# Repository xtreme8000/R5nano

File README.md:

# R5 nano

Single board computer with future Linux support, mostly intended for use as a lightweight server.

Planned SoC implementation using LiteX featuring a RISC-V CPU and 64MiB RAM.

## Gateware

TODO

## Software

Work in progress.

Firmware supports bitstream upload over USB to the FPGA at the moment.

## Hardware

* iCE40UP5k FPGA, 5280 LUTs
* 64MiB SD-RAM
* microSD card for storage
* USB port for connectivity like ethernet
* USB-C port for power, bitstream upload
* STM32F103 for initial bitstream load from either USB-C or microSD
* Debug header with FPGA+STM32 GPIO, SWD for STM32
* 52x52mm (~2x2in) board

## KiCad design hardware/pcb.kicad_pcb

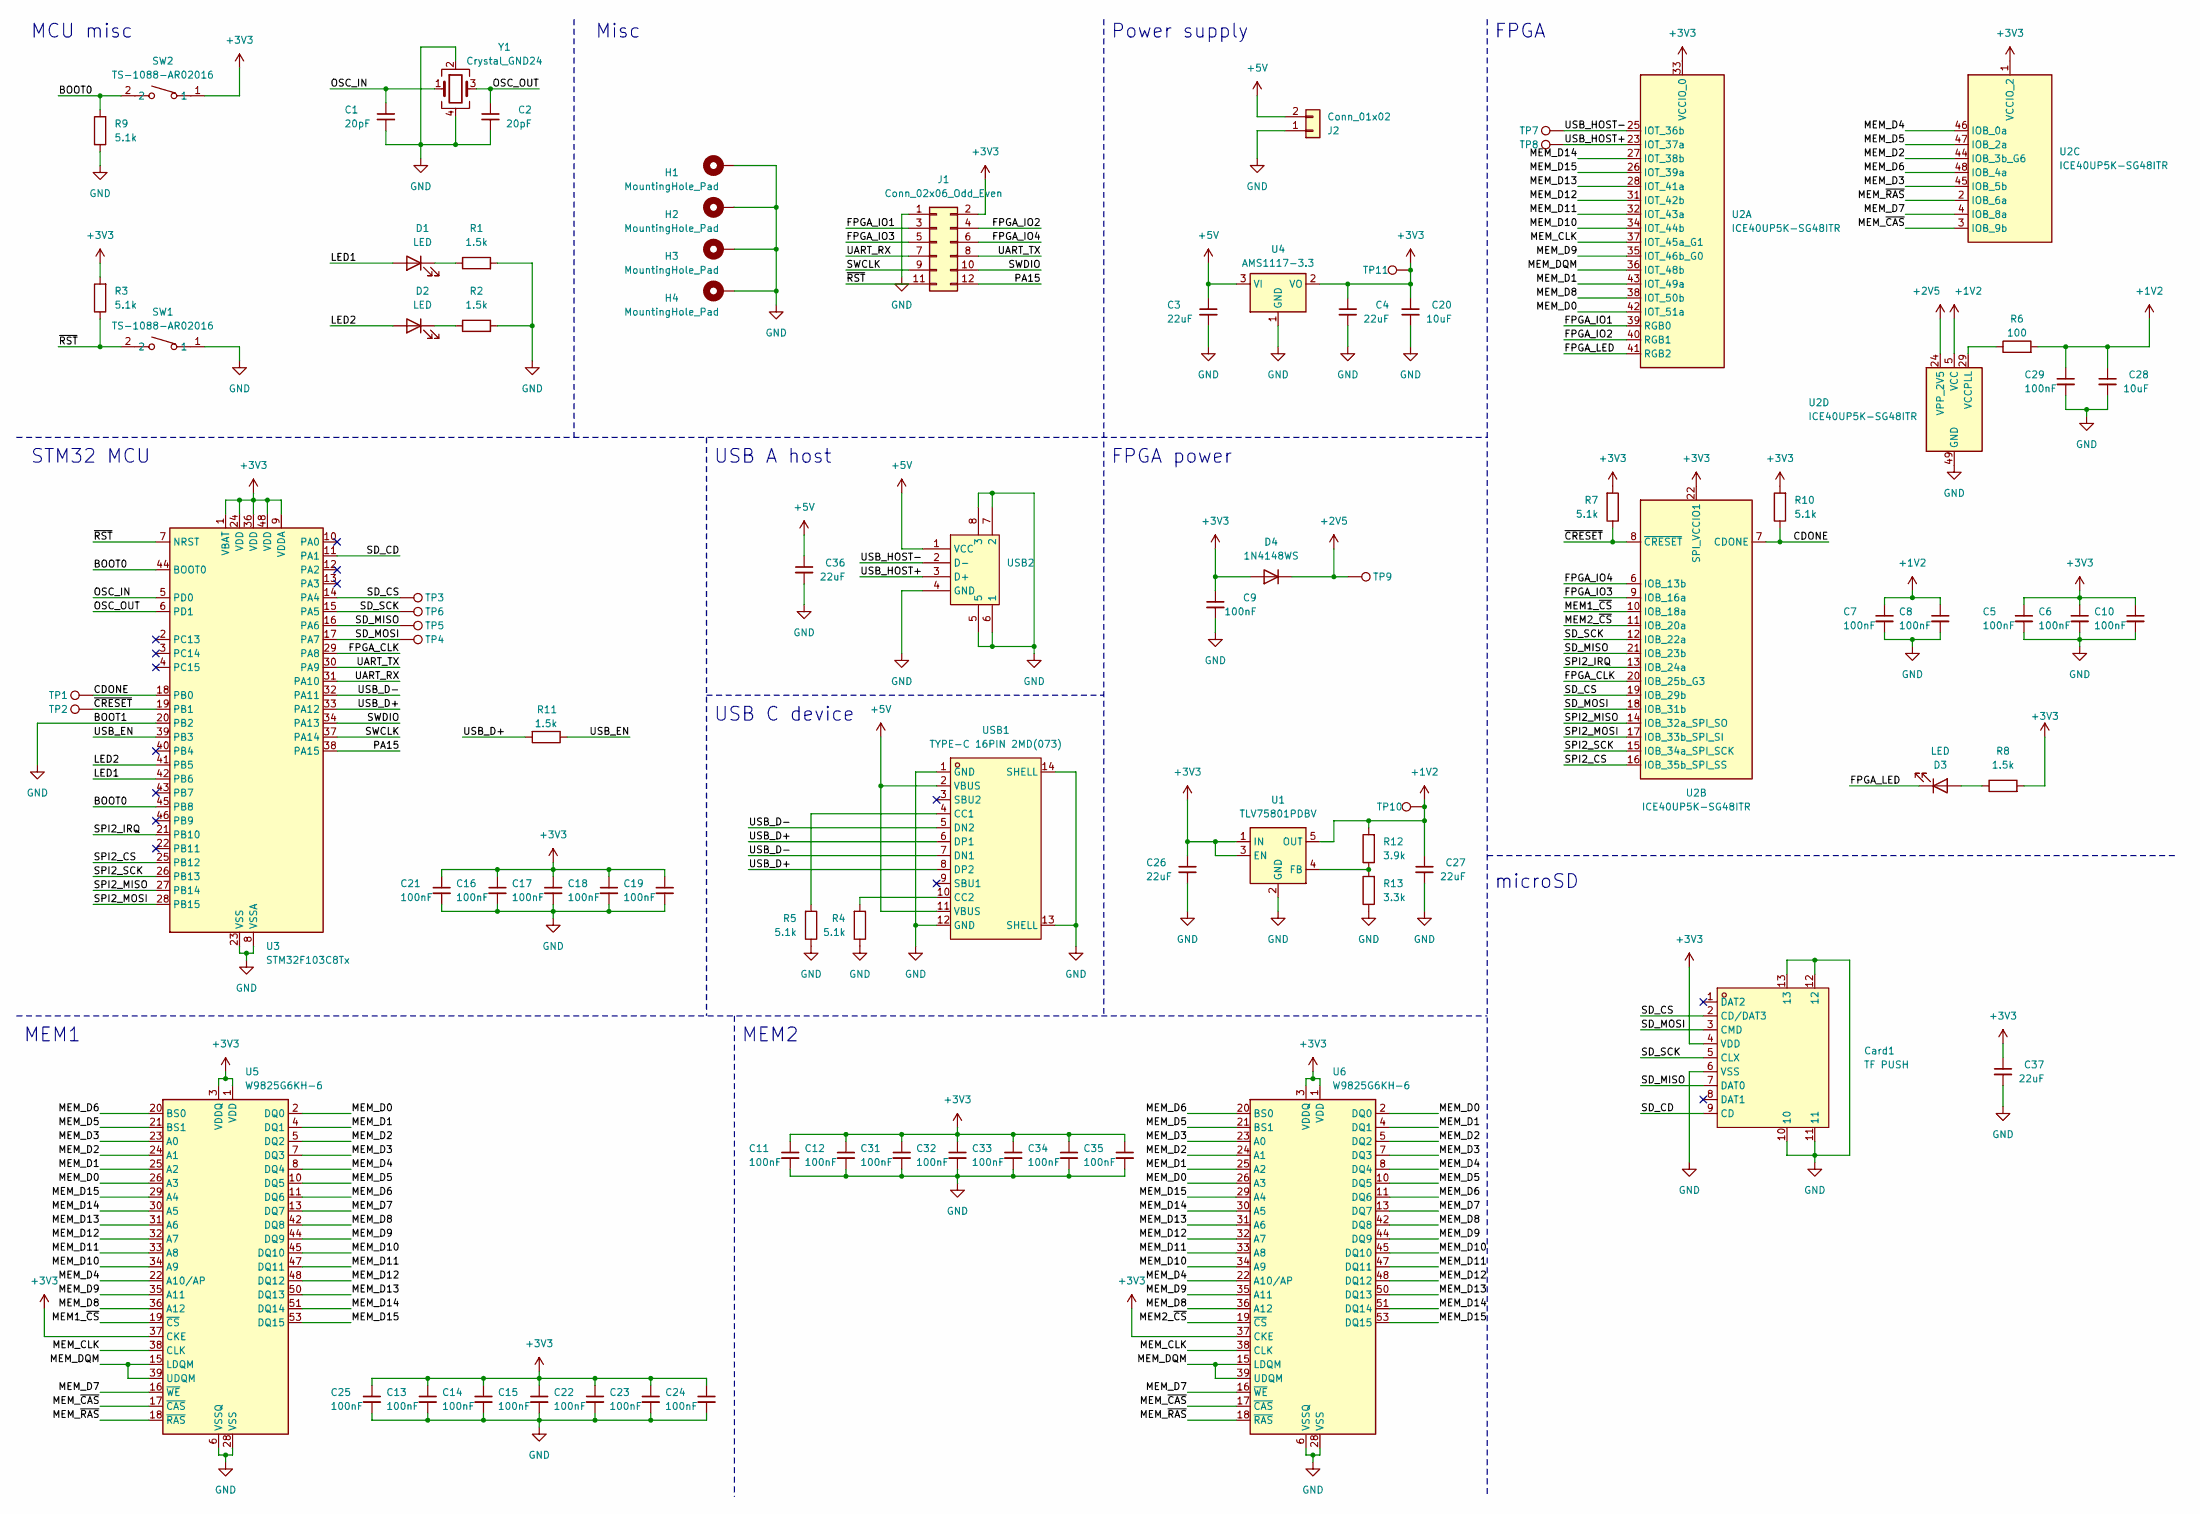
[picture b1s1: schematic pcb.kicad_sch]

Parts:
C1, C2: 20pF; C_0603_1608Metric; LCSC Part C1648
C3, C4, C26, C27, C36, C37: 22uF; C_0603_1608Metric; LCSC Part C59461
C5, C6, C7, C8, C9, C10, C11, C12, C13, C14, C15, C16, C17, C18, C19, C21, C22, C23, C24, C25, C29, C31, C32, C33, C34, C35: 100nF; C_0402_1005Metric; LCSC Part C1525
C20, C28: 10uF; C_0402_1005Metric; LCSC Part C15525
Card1: TF PUSH; TF-SMD_TF-PUSH; LCSC Part C393941
D1, D2, D3: LED; LED_0603_1608Metric; LCSC Part C2286
D4: 1N4148WS; D_SOD-323; LCSC Part C2128
H1, H2, H3, H4: MountingHole_Pad; MountingHole_2.2mm_M2_DIN965_Pad
J1: Conn_02x06_Odd_Even; PinHeader_2x06_P2.54mm_Vertical
J2: Conn_01x02; PinHeader_1x02_P2.54mm_Vertical
R1, R2, R8, R11: 1.5k; R_0603_1608Metric; LCSC Part C22843
R3, R4, R5, R7, R9, R10: 5.1k; R_0603_1608Metric; LCSC Part C23186
R6: 100; R_0402_1005Metric; LCSC Part C25076
R12: 3.9k; R_0603_1608Metric; LCSC Part C23018
R13: 3.3k; R_0603_1608Metric; LCSC Part C22978
SW1, SW2: TS-1088-AR02016; SW-SMD_L3.9-W3.0-P4.45; LCSC Part C720477
TP1, TP2, TP3, TP4, TP5, TP6, TP7, TP8, TP9, TP10, TP11: TestPoint; TestPoint_Pad_D2.0mm
U1: TLV75801PDBV; SOT-23-5; LCSC Part C2877852
U2: ICE40UP5K-SG48ITR; QFN-48-1EP_7x7mm_P0.5mm_EP5.6x5.6mm; LCSC Part C2678152
U3: STM32F103C8Tx; LQFP-48_7x7mm_P0.5mm; LCSC Part C8734
U4: AMS1117-3.3; SOT-223-3_TabPin2; LCSC Part C6186
U5, U6: W9825G6KH-6; TSOP-II-54_22.2x10.16mm_P0.8mm; LCSC Part C62246
USB1: TYPE-C 16PIN 2MD(073); USB-C-SMD_TYPE-C-6PIN-2MD-073; LCSC Part C2765186
USB2: USB-A-SMD_USB-M-21; LCSC Part C42474
Y1: Crystal_GND24; Crystal_SMD_3225-4Pin_3.2x2.5mm; LCSC Part C9002

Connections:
+1V2: C7.1, C8.1, C27.1, C28.1, C29.1, R6.2, R12.2, TP10.1, U1.5 (OUT), U2.5 (VCC), U2.30 (VCC)
+2V5: D4.1 (K), TP9.1, U2.24 (VPP_2V5)
+3V3: C4.1, C5.1, C6.1, C9.1, C10.1, C11.1, C12.1, C13.1, C14.1, C15.1, C16.1, C17.1, C18.1, C19.1, C20.1, C21.1, C22.1, C23.1, C24.1, C25.1, C26.1, C31.1, C32.1, C33.1, C34.1, C35.1, C37.1, Card1.4 (VDD), D4.2 (A), J1.2, R3.2, R7.2, R8.2, R10.2, SW2.1, TP11.1, U1.1 (IN), U1.3 (EN), U2.1 (VCCIO_2), U2.22 (SPI_VCCIO1), U2.33 (VCCIO_0), U3.1 (VBAT), U3.9 (VDDA), U3.24 (VDD), U3.36 (VDD), U3.48 (VDD), U4.2 (VO), U5.1 (VDD), U5.3 (VDDQ), U5.9 (VDDQ), U5.14 (VDD), U5.27 (VDD), U5.37 (CKE), U5.43 (VDDQ), U5.49 (VDDQ), U6.1 (VDD), U6.3 (VDDQ), U6.9 (VDDQ), U6.14 (VDD), U6.27 (VDD), U6.37 (CKE), U6.43 (VDDQ), U6.49 (VDDQ)
+5V: C3.1, C36.1, J2.2, U4.3 (VI), USB1.2 (VBUS), USB1.11 (VBUS), USB2.1 (VCC)
/BOOT0: R9.2, SW2.2, U3.44 (BOOT0), U3.45 (PB8)
/CDONE: R10.1, TP1.1, U2.7 (CDONE), U3.18 (PB0)
/FPGA_CLK: U2.20 (IOB_25b_G3), U3.29 (PA8)
/FPGA_IO1: J1.3, U2.39 (RGB0)
/FPGA_IO2: J1.4, U2.40 (RGB1)
/FPGA_IO3: J1.5, U2.9 (IOB_16a)
/FPGA_IO4: J1.6, U2.6 (IOB_13b)
/FPGA_LED: D3.1 (K), U2.41 (RGB2)
/LED1: D1.2 (A), U3.42 (PB6)
/LED2: D2.2 (A), U3.41 (PB5)
/MEM1_~CS: U2.10 (IOB_18a), U5.19 (~CS)
/MEM2_~CS: U2.11 (IOB_20a), U6.19 (~CS)
/MEM_CLK: U2.37 (IOT_45a_G1), U5.38 (CLK), U6.38 (CLK)
/MEM_D0: U2.42 (IOT_51a), U5.2 (DQ0), U5.26 (A3), U6.2 (DQ0), U6.26 (A3)
/MEM_D1: U2.43 (IOT_49a), U5.4 (DQ1), U5.25 (A2), U6.4 (DQ1), U6.25 (A2)
/MEM_D2: U2.44 (IOB_3b_G6), U5.5 (DQ2), U5.24 (A1), U6.5 (DQ2), U6.24 (A1)
/MEM_D3: U2.45 (IOB_5b), U5.7 (DQ3), U5.23 (A0), U6.7 (DQ3), U6.23 (A0)
/MEM_D4: U2.46 (IOB_0a), U5.8 (DQ4), U5.22 (A10/AP), U6.8 (DQ4), U6.22 (A10/AP)
/MEM_D5: U2.47 (IOB_2a), U5.10 (DQ5), U5.21 (BS1), U6.10 (DQ5), U6.21 (BS1)
/MEM_D6: U2.48 (IOB_4a), U5.11 (DQ6), U5.20 (BS0), U6.11 (DQ6), U6.20 (BS0)
/MEM_D7: U2.4 (IOB_8a), U5.13 (DQ7), U5.16 (~WE), U6.13 (DQ7), U6.16 (~WE)
/MEM_D8: U2.38 (IOT_50b), U5.36 (A12), U5.42 (DQ8), U6.36 (A12), U6.42 (DQ8)
/MEM_D9: U2.35 (IOT_46b_G0), U5.35 (A11), U5.44 (DQ9), U6.35 (A11), U6.44 (DQ9)
/MEM_D10: U2.34 (IOT_44b), U5.34 (A9), U5.45 (DQ10), U6.34 (A9), U6.45 (DQ10)
/MEM_D11: U2.32 (IOT_43a), U5.33 (A8), U5.47 (DQ11), U6.33 (A8), U6.47 (DQ11)
/MEM_D12: U2.31 (IOT_42b), U5.32 (A7), U5.48 (DQ12), U6.32 (A7), U6.48 (DQ12)
/MEM_D13: U2.28 (IOT_41a), U5.31 (A6), U5.50 (DQ13), U6.31 (A6), U6.50 (DQ13)
/MEM_D14: U2.27 (IOT_38b), U5.30 (A5), U5.51 (DQ14), U6.30 (A5), U6.51 (DQ14)
/MEM_D15: U2.26 (IOT_39a), U5.29 (A4), U5.53 (DQ15), U6.29 (A4), U6.53 (DQ15)
/MEM_DQM: U2.36 (IOT_48b), U5.15 (LDQM), U5.39 (UDQM), U6.15 (LDQM), U6.39 (UDQM)
/MEM_~CAS: U2.3 (IOB_9b), U5.17 (~CAS), U6.17 (~CAS)
/MEM_~RAS: U2.2 (IOB_6a), U5.18 (~RAS), U6.18 (~RAS)
/OSC_IN: C1.1, U3.5 (PD0), Y1.1
/OSC_OUT: C2.1, U3.6 (PD1), Y1.3
/PA15: J1.12, U3.38 (PA15)
/SD_CD: Card1.9 (CD), U3.11 (PA1)
/SD_CS: Card1.2 (CD/DAT3), TP3.1, U2.19 (IOB_29b), U3.14 (PA4)
/SD_MISO: Card1.7 (DAT0), TP5.1, U2.21 (IOB_23b), U3.16 (PA6)
/SD_MOSI: Card1.3 (CMD), TP4.1, U2.18 (IOB_31b), U3.17 (PA7)
/SD_SCK: Card1.5 (CLX), TP6.1, U2.12 (IOB_22a), U3.15 (PA5)
/SPI2_CS: U2.16 (IOB_35b_SPI_SS), U3.25 (PB12)
/SPI2_IRQ: U2.13 (IOB_24a), U3.21 (PB10)
/SPI2_MISO: U2.14 (IOB_32a_SPI_SO), U3.27 (PB14)
/SPI2_MOSI: U2.17 (IOB_33b_SPI_SI), U3.28 (PB15)
/SPI2_SCK: U2.15 (IOB_34a_SPI_SCK), U3.26 (PB13)
/SWCLK: J1.9, U3.37 (PA14)
/SWDIO: J1.10, U3.34 (PA13)
/UART_RX: J1.7, U3.31 (PA10)
/UART_TX: J1.8, U3.30 (PA9)
/USB_D+: R11.2, U3.33 (PA12), USB1.6 (DP1), USB1.8 (DP2)
/USB_D-: U3.32 (PA11), USB1.5 (DN2), USB1.7 (DN1)
/USB_EN: R11.1, U3.39 (PB3)
/USB_HOST+: TP8.1, U2.23 (IOT_37a), USB2.3 (D+)
/USB_HOST-: TP7.1, U2.25 (IOT_36b), USB2.2 (D-)
/~CRESET: R7.1, TP2.1, U2.8 (~CRESET), U3.19 (PB1)
/~RST: J1.11, R3.1, SW1.2, U3.7 (NRST)
GND: C1.2, C2.2, C3.2, C4.2, C5.2, C6.2, C7.2, C8.2, C9.2, C10.2, C11.2, C12.2, C13.2, C14.2, C15.2, C16.2, C17.2, C18.2, C19.2, C20.2, C21.2, C22.2, C23.2, C24.2, C25.2, C26.2, C27.2, C28.2, C29.2, C31.2, C32.2, C33.2, C34.2, C35.2, C36.2, C37.2, Card1.6 (VSS), Card1.10, Card1.11, Card1.12, Card1.13, H1.1, H2.1, H3.1, H4.1, J1.1, J2.1, R1.2, R2.2, R4.1, R5.1, R9.1, R13.1, SW1.1, U1.2 (GND), U2.49 (GND), U3.8 (VSSA), U3.20 (PB2), U3.23 (VSS), U3.35 (VSS), U3.47 (VSS), U4.1 (GND), U5.6 (VSSQ), U5.12 (VSSQ), U5.28 (VSS), U5.41 (VSS), U5.46 (VSSQ), U5.52 (VSSQ), U5.54 (VSS), U6.6 (VSSQ), U6.12 (VSSQ), U6.28 (VSS), U6.41 (VSS), U6.46 (VSSQ), U6.52 (VSSQ), U6.54 (VSS), USB1.1 (GND), USB1.12 (GND), USB1.13 (SHELL), USB1.14 (SHELL), USB2.4 (GND), USB2.5, USB2.6 (1), USB2.7 (2), USB2.8 (3), Y1.2, Y1.4
unnamed: D1.1 (K), R1.1
unnamed: D2.1 (K), R2.1
unnamed: D3.2 (A), R8.1
unnamed: R12.1, R13.2, U1.4 (FB)
unnamed: R6.1, U2.29 (VCCPLL)
unnamed: R5.2, USB1.4 (CC1)
unnamed: R4.2, USB1.10 (CC2)

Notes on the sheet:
microSD
MEM1
Misc
STM32 MCU
USB A host
MCU misc
MEM2
USB C device
Power supply
FPGA power
FPGA

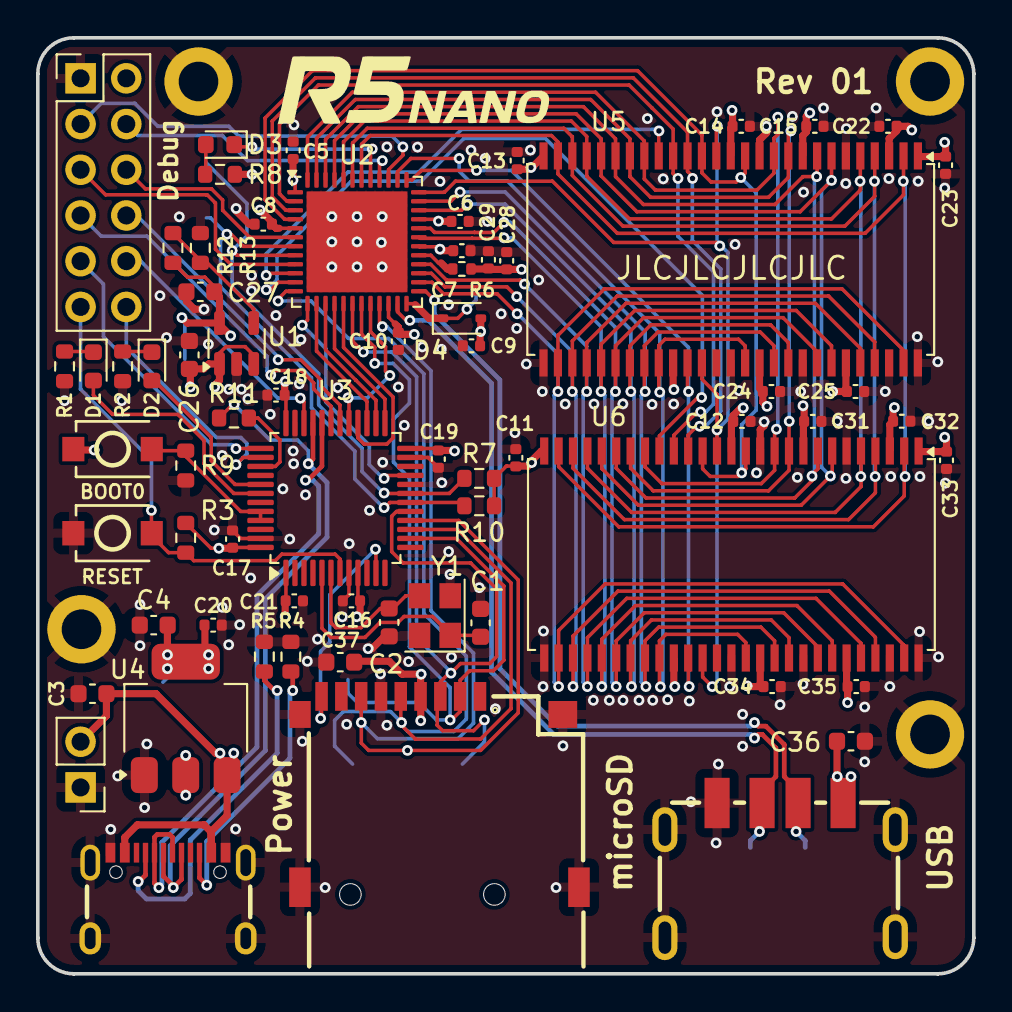
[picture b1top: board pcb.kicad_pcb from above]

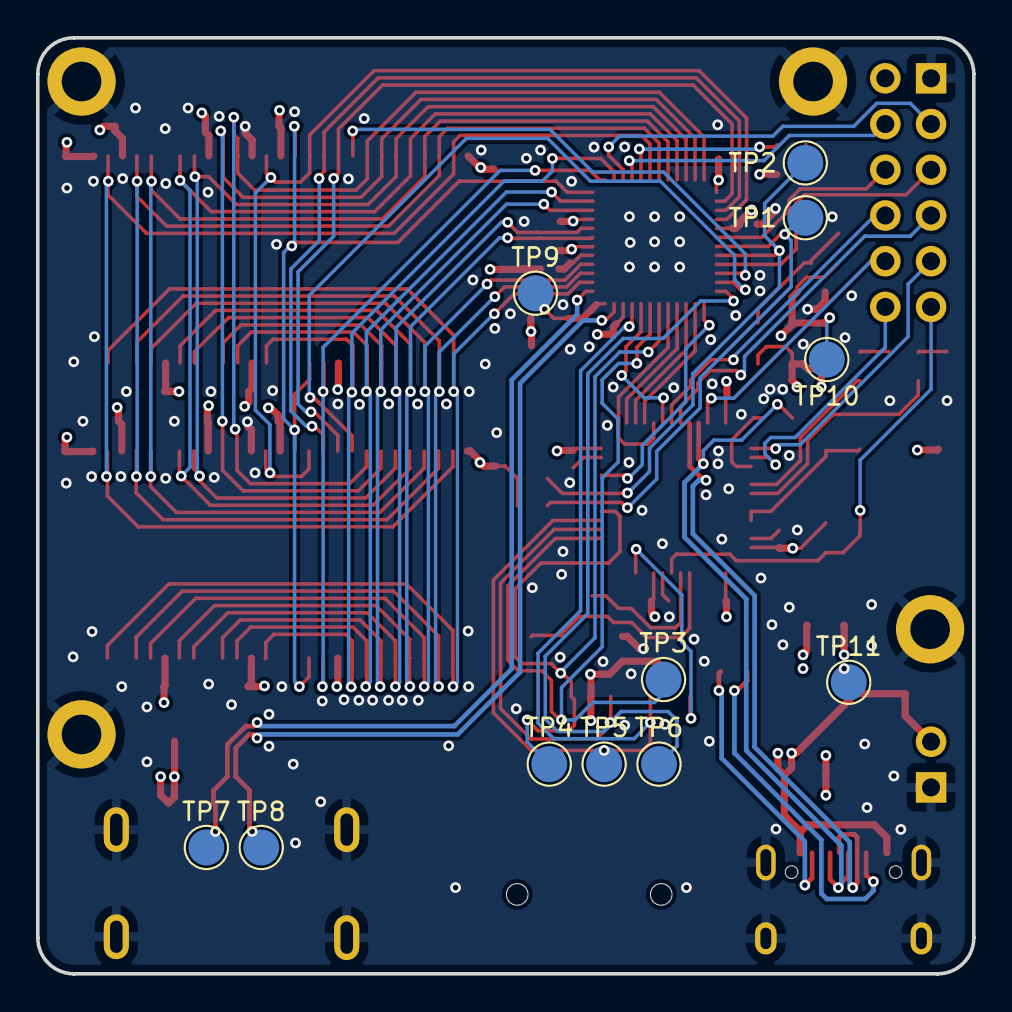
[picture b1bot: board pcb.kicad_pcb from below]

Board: 4 copper layers, 52.0 x 52.0 mm, 82 parts (11 on the bottom side), 68 nets.

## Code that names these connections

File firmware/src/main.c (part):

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#define PIN_SPI_SS GPIO12

#define PORT_CDONE GPIOB
#define PIN_CDONE GPIO0

#define PORT_USB_EN GPIOB
#define PIN_USB_EN GPIO3

#define PORT_LED1 GPIOB
#define PIN_LED1 GPIO6

#define PORT_LED2 GPIOB
#define PIN_LED2 GPIO5

uint8_t usbd_control_buffer[64]; // buffer for control requests

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}

void task_usb(void* args) {
	gpio_clear(PORT_USB_EN, PIN_USB_EN);
	vTaskDelay(pdMS_TO_TICKS(100));
	gpio_set(PORT_USB_EN, PIN_USB_EN);

	usbd_device* usbd_dev = usbd_init(
		&st_usbfs_v1_usb_driver, &dev_descr, &usb_config, usb_strings, 2,
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
void task_blink(void* args) {
	while(1) {
		gpio_toggle(PORT_LED1, PIN_LED1);
		vTaskDelay(pdMS_TO_TICKS(500));
	}
}
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		payload_transmitted = 0;
		xQueueSend(available_buffers, &e, portMAX_DELAY);

		gpio_set(PORT_LED2, PIN_LED2);

		gpio_clear(PORT_CRESET_B, PIN_CRESET_B);
		gpio_clear(PORT_SPI_SS, PIN_SPI_SS);
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
		spi_wait_idle(SPI2);

		uint8_t success = gpio_get(PORT_CDONE, PIN_CDONE) ? 1 : 0;
		xQueueSend(usb_host_interrupt, &success, portMAX_DELAY);

		gpio_clear(PORT_LED2, PIN_LED2);
	}
}

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
	// usb setup
	gpio_set_mode(PORT_USB_EN, GPIO_MODE_OUTPUT_2_MHZ, GPIO_CNF_OUTPUT_PUSHPULL,
				  PIN_USB_EN);
	gpio_clear(PORT_USB_EN, PIN_USB_EN);

	// blink setup
	gpio_set_mode(PORT_LED1, GPIO_MODE_OUTPUT_2_MHZ, GPIO_CNF_OUTPUT_PUSHPULL,
				  PIN_LED1);
	gpio_clear(PORT_LED1, PIN_LED1);
	gpio_set_mode(PORT_LED2, GPIO_MODE_OUTPUT_2_MHZ, GPIO_CNF_OUTPUT_PUSHPULL,
				  PIN_LED2);
	gpio_clear(PORT_LED2, PIN_LED2);

	// upload setup
	rcc_periph_clock_enable(RCC_SPI2);
	rcc_periph_clock_enable(RCC_DMA1);

	gpio_set_mode(GPIO_BANK_SPI2_SCK, GPIO_MODE_OUTPUT_50_MHZ,
				  GPIO_CNF_OUTPUT_ALTFN_PUSHPULL, GPIO_SPI2_SCK);
	gpio_set_mode(GPIO_BANK_SPI2_MOSI, GPIO_MODE_OUTPUT_50_MHZ,
				  GPIO_CNF_OUTPUT_ALTFN_PUSHPULL, GPIO_SPI2_MOSI);
	gpio_set_mode(GPIO_BANK_SPI2_MISO, GPIO_MODE_INPUT, GPIO_CNF_INPUT_FLOAT,
				  GPIO_SPI2_MISO);

	spi_init_master(
		SPI2, SPI_CR1_BAUDRATE_FPCLK_DIV_32, SPI_CR1_CPOL_CLK_TO_1_WHEN_IDLE,
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				  GPIO_CNF_OUTPUT_PUSHPULL, PIN_CRESET_B);
	gpio_set_mode(PORT_SPI_SS, GPIO_MODE_OUTPUT_50_MHZ,
				  GPIO_CNF_OUTPUT_PUSHPULL, PIN_SPI_SS);
	gpio_set_mode(PORT_CDONE, GPIO_MODE_INPUT, GPIO_CNF_INPUT_FLOAT, PIN_CDONE);
	gpio_set(PORT_CRESET_B, PIN_CRESET_B);
	gpio_set(PORT_SPI_SS, PIN_SPI_SS);

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
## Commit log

2025-09-18 PCB files + readme
2025-09-18 Change scale
2025-09-18 mcu firmware
